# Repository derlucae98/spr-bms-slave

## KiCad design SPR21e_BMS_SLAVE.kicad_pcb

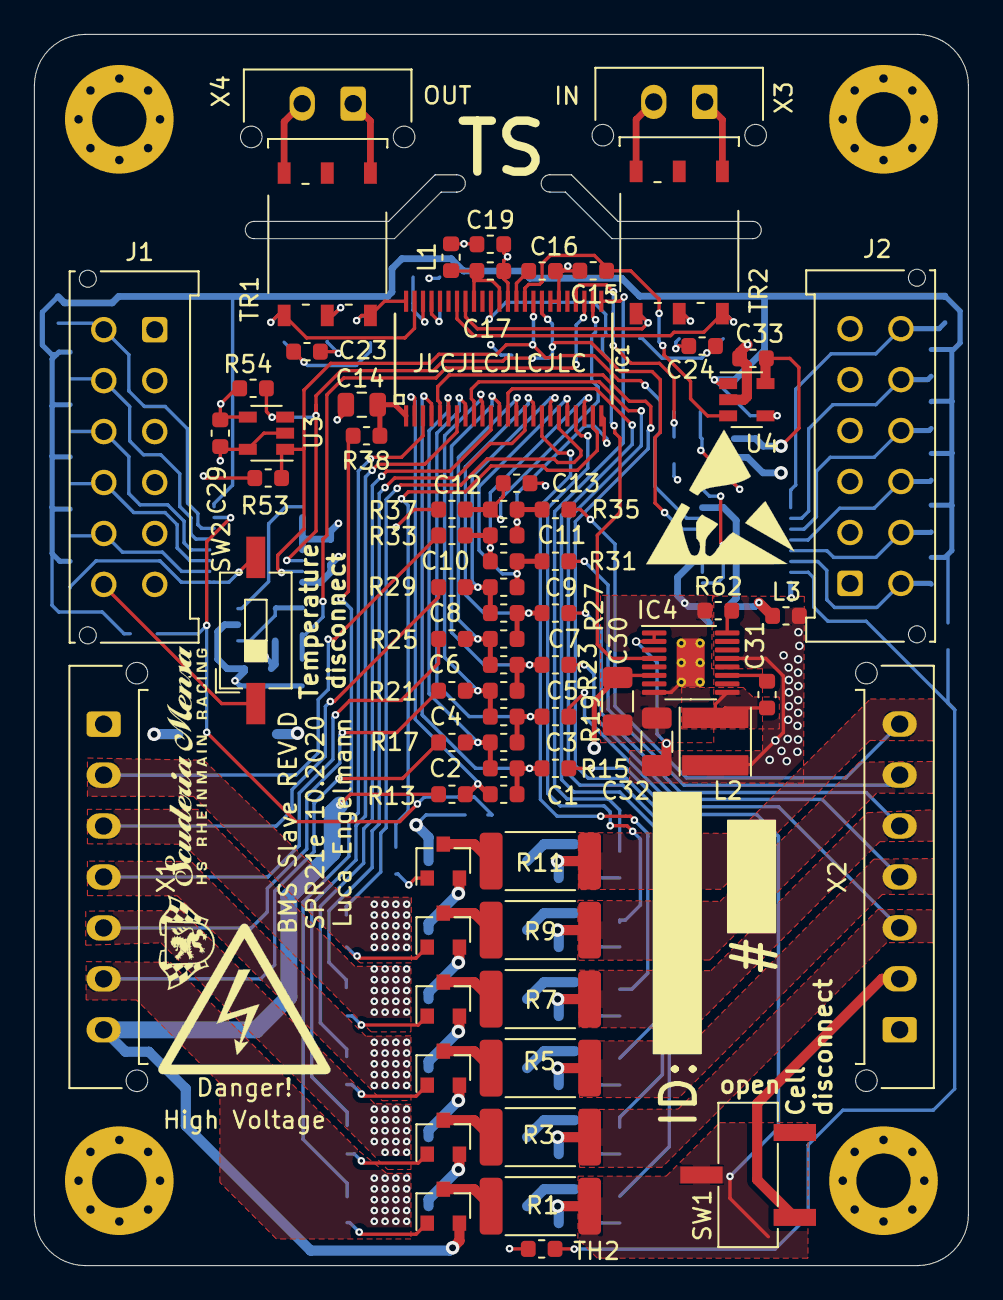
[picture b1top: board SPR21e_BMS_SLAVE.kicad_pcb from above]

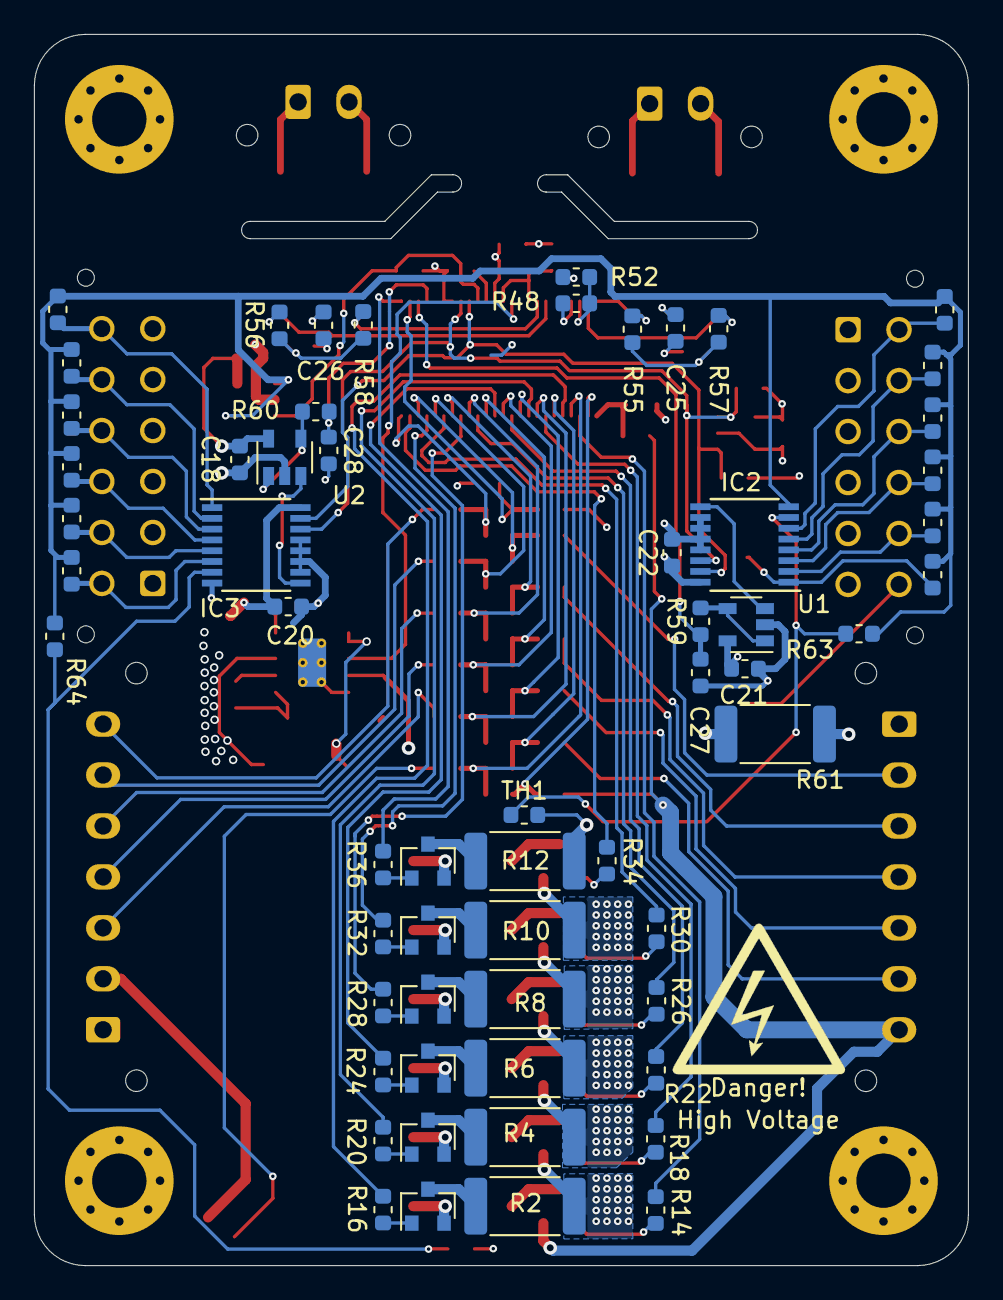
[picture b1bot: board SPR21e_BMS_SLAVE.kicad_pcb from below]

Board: 4 copper layers, 55.0 x 72.5 mm, 139 parts (60 on the bottom side), 112 nets.

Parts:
C1, C2, C3, C4, C5, C6, C7, C8, C9, C10, C11, C12, C13, C23, C24, C25, C26, C27, C28: 10n; C_0603_1608Metric
C14: 100n; C_0805_2012Metric
C15, C16, C17, C18, C19, C20, C21, C29, C33: 1u; C_0603_1608Metric
C22: 1µ; C_0603_1608Metric
C30: 2µ2; C_1206_3216Metric
C31: 220n; C_0603_1608Metric
C32: 22µ; C_1206_3216Metric
IC1: LTC6811-1; LTC6804_SSOP
IC2, IC3: LTC1380GN; SSOP-16_3.9x4.9mm_P0.635mm
IC4: LT3990-5MSE; MSOP-16-1EP_3x4.039mm_P0.5mm_EP1.651x2.845mm_ThermalVias
J1: TEMPSEN A; Molex_Micro-Fit_3.0_43045-1212_2x06_P3.00mm_Vertical
J2: TEMPSEN B; Molex_Micro-Fit_3.0_43045-1212_2x06_P3.00mm_Vertical
L1, L3: 2u2; L_0603_1608Metric
L2: 33µ; L_Taiyo-Yuden_NR-40xx
M1, M2, M3, M4: MOUNT; MountingHole_3.2mm_M3_Pad_Via
Q1, Q2, Q3, Q4, Q5, Q6, Q7, Q8, Q9, Q10, Q11, Q12: BSS308PE; SOT-23
R1, R2, R3, R4, R5, R6, R7, R8, R9, R10, R11, R12: 33R; R_2512_6332Metric
R13, R15, R17, R19, R21, R23, R25, R27, R29, R31, R33, R35, R37, R38, R59, R60: 100R; R_0603_1608Metric
R14, R16, R18, R20, R22, R24, R26, R28, R30, R32, R34, R36, R53, R54: 3k3; R_0603_1608Metric
R39, R40, R41, R42, R43, R44, R45, R46, R47, R49, R50, R51, R63, R64: 18k; R_0603_1608Metric
R48: 2k8; R_0603_1608Metric
R52: 1k21; R_0603_1608Metric
R55, R56, R57, R58: 51R; R_0603_1608Metric
R61: 220R; R_2512_6332Metric
R62: 374k; R_0603_1608Metric
S1: ESD_SYMBOL; ESD-Logo_8.9x8mm_SilkScreen
S2: SCUDERIA_LOGO; Logo_klein
S3: HV LOGO; High Voltage Logo
SW1: CELL_DISC; JS102011SCQN
SW2: TEMP_DISC; SW_DIP_SPSTx01_Slide_6.7x4.1mm_W8.61mm_P2.54mm_LowProfile
TH1, TH2: 10k; R_0603_1608Metric
TR1, TR2: SM91502AL
U1, U2, U4: TLV376IDBVR; SOT-23-5
U3: 24AA02UID; SOT-23-5
X1: CELL EVEN; Molex_Micro-Fit_3.0_43650-0715_1x07_P3.00mm_Vertical
X2: CELL ODD; Molex_Micro-Fit_3.0_43650-0715_1x07_P3.00mm_Vertical
X3: ISO_INPUT; Molex_Micro-Fit_3.0_43650-0215_1x02_P3.00mm_Vertical
X4: ISO_OUTPUT; Molex_Micro-Fit_3.0_43650-0215_1x02_P3.00mm_Vertical

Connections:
+5V: C19.1, C29.1, C32.2, IC4.1, IC4.2, IC4.13, L1.2, L2.2, L3.1, R53.1, R54.1, U3.4
+5VA: C18.1, C20.1, C21.1, C22.1, C33.1, IC2.16, IC3.16, L3.2, U1.5, U2.5, U4.5
/BMS IC/ADC1: C27.1, IC1.27, R59.1
/BMS IC/ADC2: C28.1, IC1.28, R60.1
/BMS IC/BATT_C1: Q12.2, R11.2, R35.2, X2.7
/BMS IC/BATT_C2: Q11.2, R10.2, R33.2, X1.2
/BMS IC/BATT_C3: Q10.2, R9.2, R31.2, X2.6
/BMS IC/BATT_C4: Q9.2, R8.2, R29.2, X1.3
/BMS IC/BATT_C5: Q8.2, R7.2, R27.2, X2.5
/BMS IC/BATT_C6: Q7.2, R6.2, R25.2, X1.4
/BMS IC/BATT_C7: Q6.2, R5.2, R23.2, X2.4
/BMS IC/BATT_C8: Q5.2, R4.2, R21.2, X1.5
/BMS IC/BATT_C9: Q4.2, R3.2, R19.2, X2.3
/BMS IC/BATT_C10: Q3.2, R2.2, R17.2, X1.6
/BMS IC/BATT_C11: Q2.2, R1.2, R15.2, SW1.2
/BMS IC/BATT_C12: Q1.2, R13.2, R38.2, R61.2, X1.7
/BMS IC/C0: C12.2, C13.1, IC1.26, R37.1
/BMS IC/C1: C11.2, C12.1, IC1.24, R35.1
/BMS IC/C2: C10.2, C11.1, IC1.22, R33.1
/BMS IC/C3: C9.2, C10.1, IC1.20, R31.1
/BMS IC/C4: C8.2, C9.1, IC1.18, R29.1
/BMS IC/C5: C7.2, C8.1, IC1.16, R27.1
/BMS IC/C6: C6.2, C7.1, IC1.14, R25.1
/BMS IC/C7: C5.2, C6.1, IC1.12, R23.1
/BMS IC/C8: C4.2, C5.1, IC1.10, R21.1
/BMS IC/C9: C3.2, C4.1, IC1.8, R19.1
/BMS IC/C10: C2.2, C3.1, IC1.6, R17.1
/BMS IC/C11: C1.2, C2.1, IC1.4, R15.1
/BMS IC/C12: C1.1, IC1.2, R13.1
/BMS IC/ENABLE: IC1.38, IC4.4
/BMS IC/ISO_INPUT_A: TR2.1, X3.1
/BMS IC/ISO_INPUT_B: TR2.3, X3.2
/BMS IC/ISO_OUTPUT_A: TR1.1, X4.1
/BMS IC/ISO_OUTPUT_B: TR1.3, X4.2
/BMS IC/REF: IC2.8, R39.1, R40.1, R41.1, R42.1, R43.1, R44.1, R45.1, R46.1, R47.1, R49.1, R50.1, R51.1, R63.1, R64.1, U4.1, U4.4
/BMS IC/S1: IC1.25, R36.1
/BMS IC/S2: IC1.23, R34.1
/BMS IC/S3: IC1.21, R32.1
/BMS IC/S4: IC1.19, R30.1
/BMS IC/S5: IC1.17, R28.1
/BMS IC/S6: IC1.15, R26.1
/BMS IC/S7: IC1.13, R24.1
/BMS IC/S8: IC1.11, R22.1
/BMS IC/S9: IC1.9, R20.1
/BMS IC/S10: IC1.7, R18.1
/BMS IC/S11: IC1.5, R16.1
/BMS IC/S12: IC1.3, R14.1
/BMS IC/SCL: IC1.33, IC2.15, IC3.15, R53.2, U3.1
/BMS IC/SDA: IC1.32, IC2.14, IC3.14, R54.2, U3.3
/BMS IC/TEMP1: IC3.7, R64.2, TH2.1
/BMS IC/TEMP2: IC2.7, R63.2, TH1.1
/BMS IC/TEMPSEN1A: IC2.1, R51.2, SW2.2
/BMS IC/TEMPSEN2A: IC2.2, J1.11, R50.2
/BMS IC/TEMPSEN3A: IC2.3, J1.10, R49.2
/BMS IC/TEMPSEN4A: IC2.4, J1.9, R47.2
/BMS IC/TEMPSEN5A: IC2.5, J1.8, R46.2
/BMS IC/TEMPSEN6A: IC2.6, J1.7, R45.2
/BMS IC/TEMPSEN7A: IC3.1, J2.12, R44.2
/BMS IC/TEMPSEN8A: IC3.2, J2.11, R43.2
/BMS IC/TEMPSEN9A: IC3.3, J2.10, R42.2
/BMS IC/TEMPSEN10A: IC3.4, J2.9, R41.2
/BMS IC/TEMPSEN11A: IC3.5, J2.8, R40.2
/BMS IC/TEMPSEN12A: IC3.6, J2.7, R39.2
GND: C13.2, C14.2, C15.2, C16.2, C17.2, C18.2, C19.2, C20.2, C21.2, C22.2, C23.2, C24.2, C25.2, C26.2, C27.2, C28.2, C29.2, C30.1, C32.1, C33.2, IC1.30, IC1.31, IC1.36, IC2.10, IC2.11, IC2.12, IC2.13, IC3.8, IC3.10, IC3.11, IC3.12, IC3.13, IC4.8, IC4.17, J1.1, J1.2, J1.3, J1.4, J1.5, J1.6, J2.1, J2.2, J2.3, J2.4, J2.5, J2.6, R12.2, R37.2, R52.2, R62.1, TH1.2, TH2.2, U1.2, U2.2, U3.2, U3.5, U4.2, X1.1
unnamed: C14.1, IC1.1, R38.1
unnamed: C15.1, IC1.34, U4.3
unnamed: C16.1, IC1.35
unnamed: C17.1, IC1.37, IC1.40, L1.1
unnamed: C23.1, R55.2, R57.2
unnamed: C24.1, R56.2, R58.2
unnamed: C25.1, TR1.5
unnamed: C26.1, TR2.5
unnamed: C30.2, IC4.6, R61.1
unnamed: C31.1, IC4.9, L2.1
unnamed: C31.2, IC4.11
unnamed: IC1.41, R58.1, TR2.4
unnamed: IC1.42, R56.1, TR2.6
unnamed: IC1.45, R48.1
unnamed: IC1.46, R48.2, R52.1
unnamed: IC1.47, R57.1, TR1.4
unnamed: IC1.48, R55.1, TR1.6
unnamed: IC2.9, U1.3
unnamed: IC3.9, U2.3
unnamed: IC4.16, R62.2
unnamed: J1.12, SW2.1
unnamed: Q1.1, R14.2
unnamed: Q1.3, R1.1
unnamed: Q2.1, R16.2
unnamed: Q2.3, R2.1
unnamed: Q3.1, R18.2
unnamed: Q3.3, R3.1
unnamed: Q4.1, R20.2
unnamed: Q4.3, R4.1
unnamed: Q5.1, R22.2
unnamed: Q5.3, R5.1
unnamed: Q6.1, R24.2
unnamed: Q6.3, R6.1
unnamed: Q7.1, R26.2
unnamed: Q7.3, R7.1
unnamed: Q8.1, R28.2
unnamed: Q8.3, R8.1
unnamed: Q9.1, R30.2
unnamed: Q9.3, R9.1
unnamed: Q10.1, R32.2
unnamed: Q10.3, R10.1
unnamed: Q11.1, R34.2
unnamed: Q11.3, R11.1
unnamed: Q12.1, R36.2
unnamed: Q12.3, R12.1
unnamed: R59.2, U1.1, U1.4
unnamed: R60.2, U2.1, U2.4
unnamed: SW1.1, X2.2

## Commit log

2025-05-16 Add project
